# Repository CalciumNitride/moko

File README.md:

#  $` 10^{-13} `$ (moko keyboard)

30% split keyboard

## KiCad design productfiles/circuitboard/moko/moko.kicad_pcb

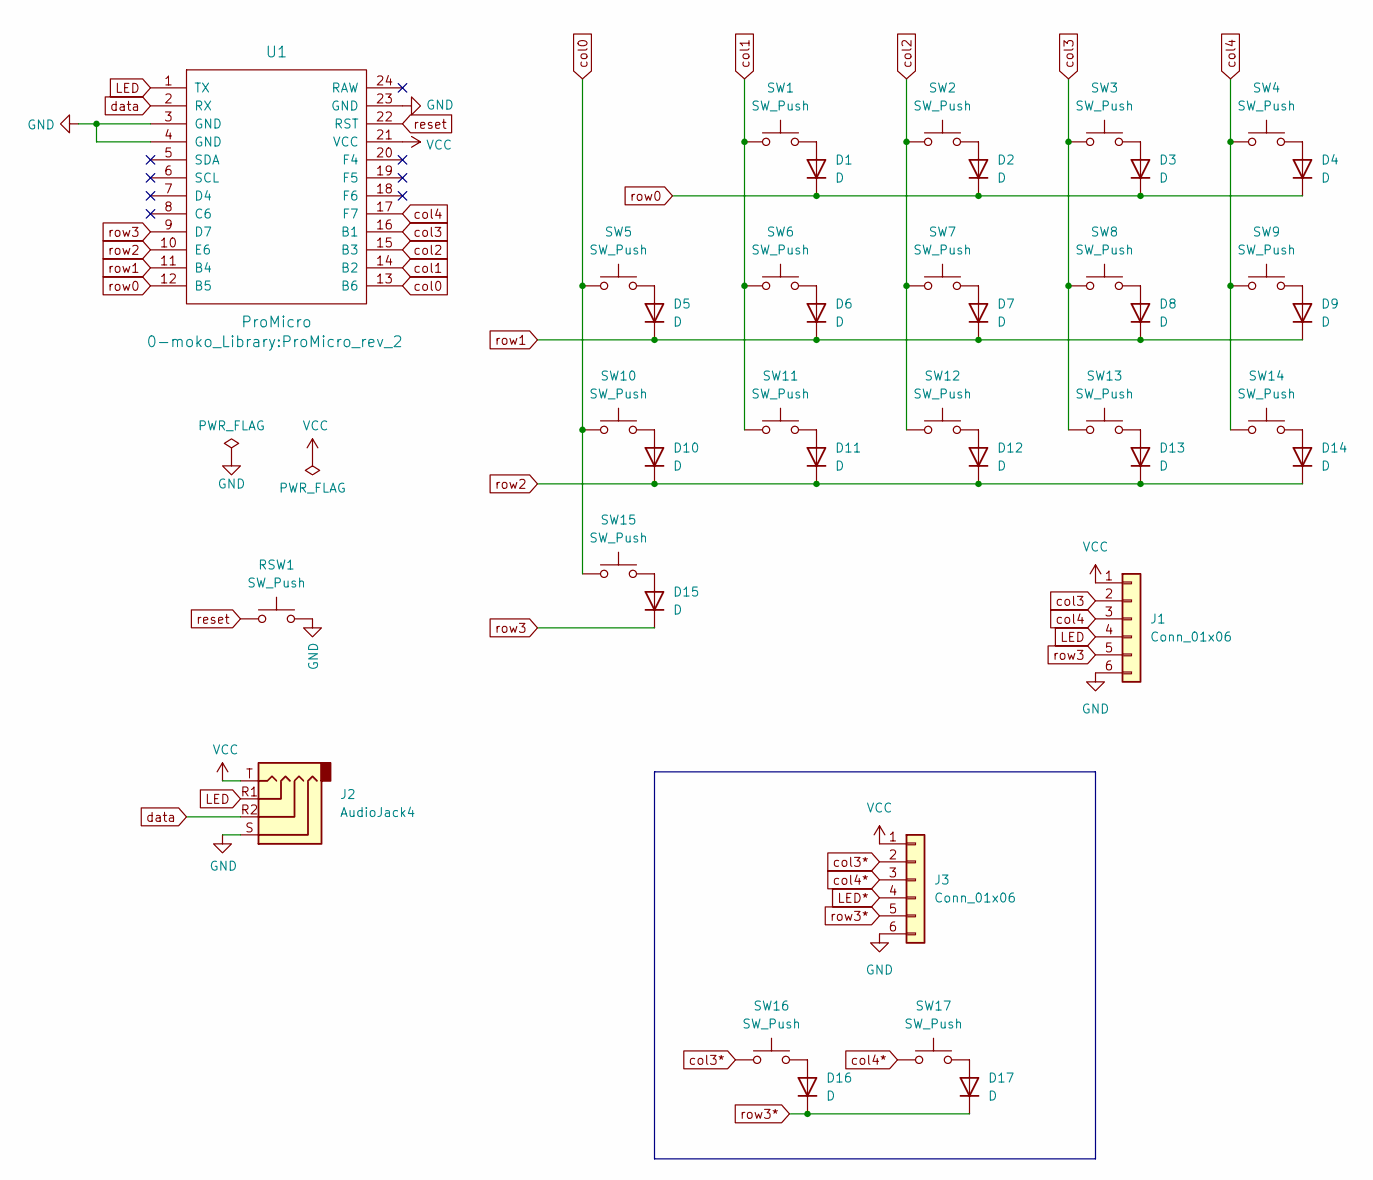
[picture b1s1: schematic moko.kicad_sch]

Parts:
D1, D2, D3, D4, D5, D6, D7, D8, D9, D10, D11, D12, D13, D14, D15, D16, D17: D; D3_SMD_rev
J1, J3: Conn_01x06; board_conector_6pin_th
J2: AudioJack4; MJ-4PP-9_rev_2
RSW1: SW_Push; ResetSW
SW1, SW2, SW3, SW4, SW5, SW6, SW7, SW8, SW9, SW10, SW11, SW12, SW13, SW14, SW15, SW16, SW17: SW_Push; CherryMX_Hotswap
U1: ProMicro; ProMicro_rev_2

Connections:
GND: J1.6, J2.S, J3.6, RSW1.2, U1.3 (GND), U1.4 (GND), U1.23 (GND)
LED: J1.4, J2.R1, U1.1 (TX)
LED*: J3.4
unnamed: D1.2 (A), SW1.2
unnamed: D2.2 (A), SW2.2
unnamed: D3.2 (A), SW3.2
unnamed: D4.2 (A), SW4.2
unnamed: D5.2 (A), SW5.2
unnamed: D6.2 (A), SW6.2
unnamed: D7.2 (A), SW7.2
unnamed: D8.2 (A), SW8.2
unnamed: D9.2 (A), SW9.2
unnamed: D10.2 (A), SW10.2
unnamed: D11.2 (A), SW11.2
unnamed: D12.2 (A), SW12.2
unnamed: D13.2 (A), SW13.2
unnamed: D14.2 (A), SW14.2
unnamed: D15.2 (A), SW15.2
unnamed: D16.2 (A), SW16.2
unnamed: D17.2 (A), SW17.2
VCC: J1.1, J2.T, J3.1, U1.21 (VCC)
col0: SW5.1, SW10.1, SW15.1, U1.13 (B6)
col1: SW1.1, SW6.1, SW11.1, U1.14 (B2)
col2: SW2.1, SW7.1, SW12.1, U1.15 (B3)
col3: J1.2, SW3.1, SW8.1, SW13.1, U1.16 (B1)
col3*: J3.2, SW16.1
col4: J1.3, SW4.1, SW9.1, SW14.1, U1.17 (F7)
col4*: J3.3, SW17.1
data: J2.R2, U1.2 (RX)
reset: RSW1.1, U1.22 (RST)
row0: D1.1 (K), D2.1 (K), D3.1 (K), D4.1 (K), U1.12 (B5)
row1: D5.1 (K), D6.1 (K), D7.1 (K), D8.1 (K), D9.1 (K), U1.11 (B4)
row2: D10.1 (K), D11.1 (K), D12.1 (K), D13.1 (K), D14.1 (K), U1.10 (E6)
row3: D15.1 (K), J1.5, U1.9 (D7)
row3*: D16.1 (K), D17.1 (K), J3.5

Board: 2 copper layers, 39 parts (1 on the bottom side), 34 nets, no tracks yet.

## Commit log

2023-10-18 add README.md
2023-10-25 add case data
2023-10-25 update case data
2023-11-17 add circuitboard layout
2023-12-11 Auto stash before merge of "main" and "origin/main"
2023-12-12 repair case file and add kicad files
2023-12-12 update casefile
2023-12-12 fix case file
2023-12-13 update mid plate
2024-01-05 add case data (for using spacer)
2024-04-16 update kicad files
2024-06-19 update kicad for new ver
2024-08-19 update circuit diagram
2024-12-25 update footprint
2025-04-16 add choc layout
2025-08-10 create pcb data
2025-08-10 fix pcb and sch
2025-12-24 board upd8
2026-02-11 add gitignore
